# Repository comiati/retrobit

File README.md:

# RetroBit Game Console

This is a mix of retro game console with new technologies.

## Hardware

This is ARM9 processor running at 454Mhz with enough power to run linux and still in handsolder friendly TQFP package, which allow hobby DIY approach. RetroBit is even on 2 layer PCB and running at full speed.

######

- i.MX233 128-QFP Processor ARM926EJ-S runs up to 454MHz
- Memory 64MB DDR SDRAM (32Mx16)
- One USB host.
- Four input game pad controls.
- One degub UART.
- Composite video output.
- Stereo sound output.
- Micro SD Card.
- Power suply with power button and Led.
- Reset button.

## Software

ArchLinux package for the moment is with most advanced Kernel and enabled features so this is our choice for the moment to build examples.

This hardware is based on OLinuxXino of www.olimex.com
https://github.com/OLIMEX/OLINUXINO/tree/master/SOFTWARE/iMX233

For more informations send email to: fabianotraple@gmail.com

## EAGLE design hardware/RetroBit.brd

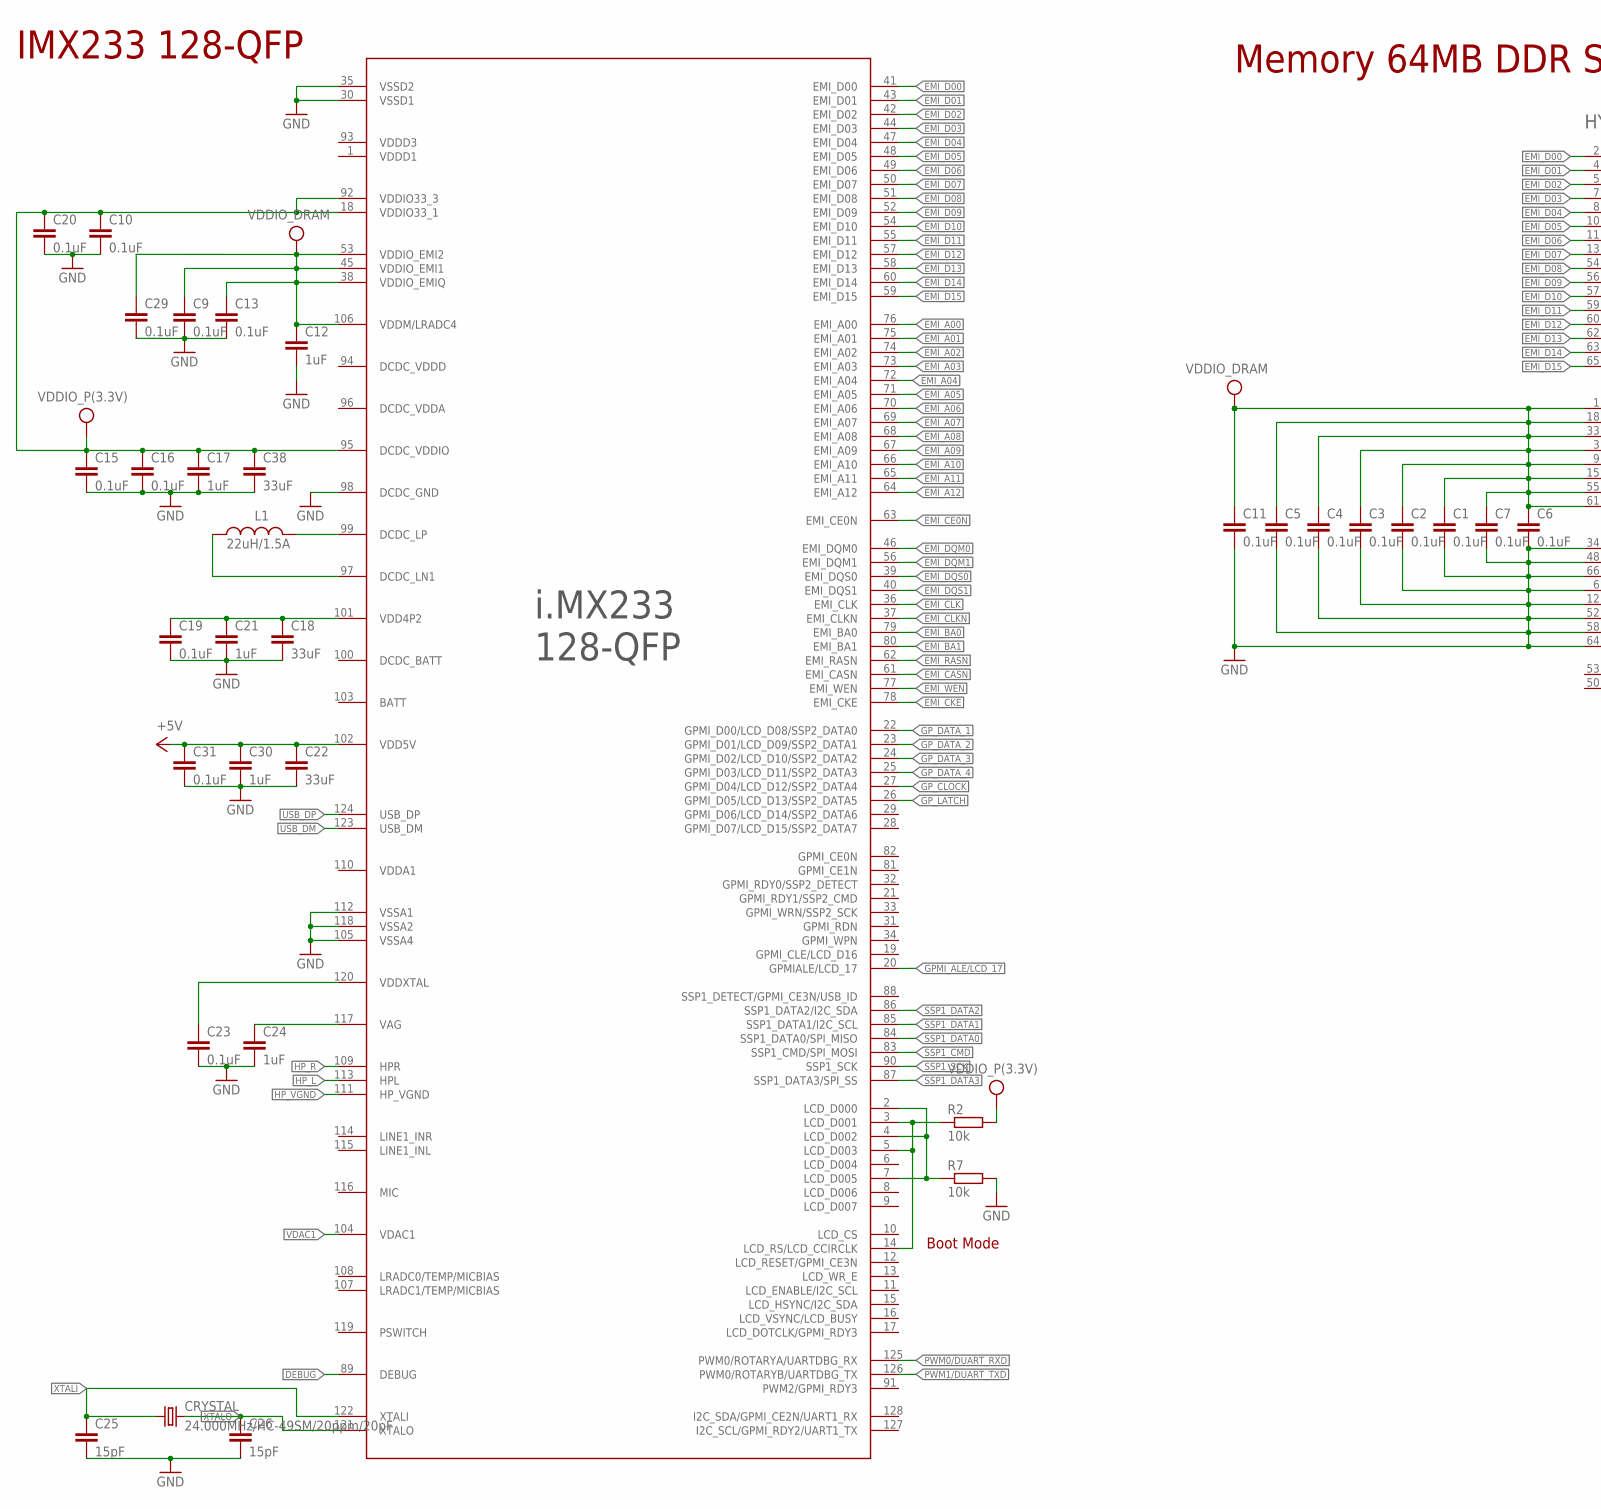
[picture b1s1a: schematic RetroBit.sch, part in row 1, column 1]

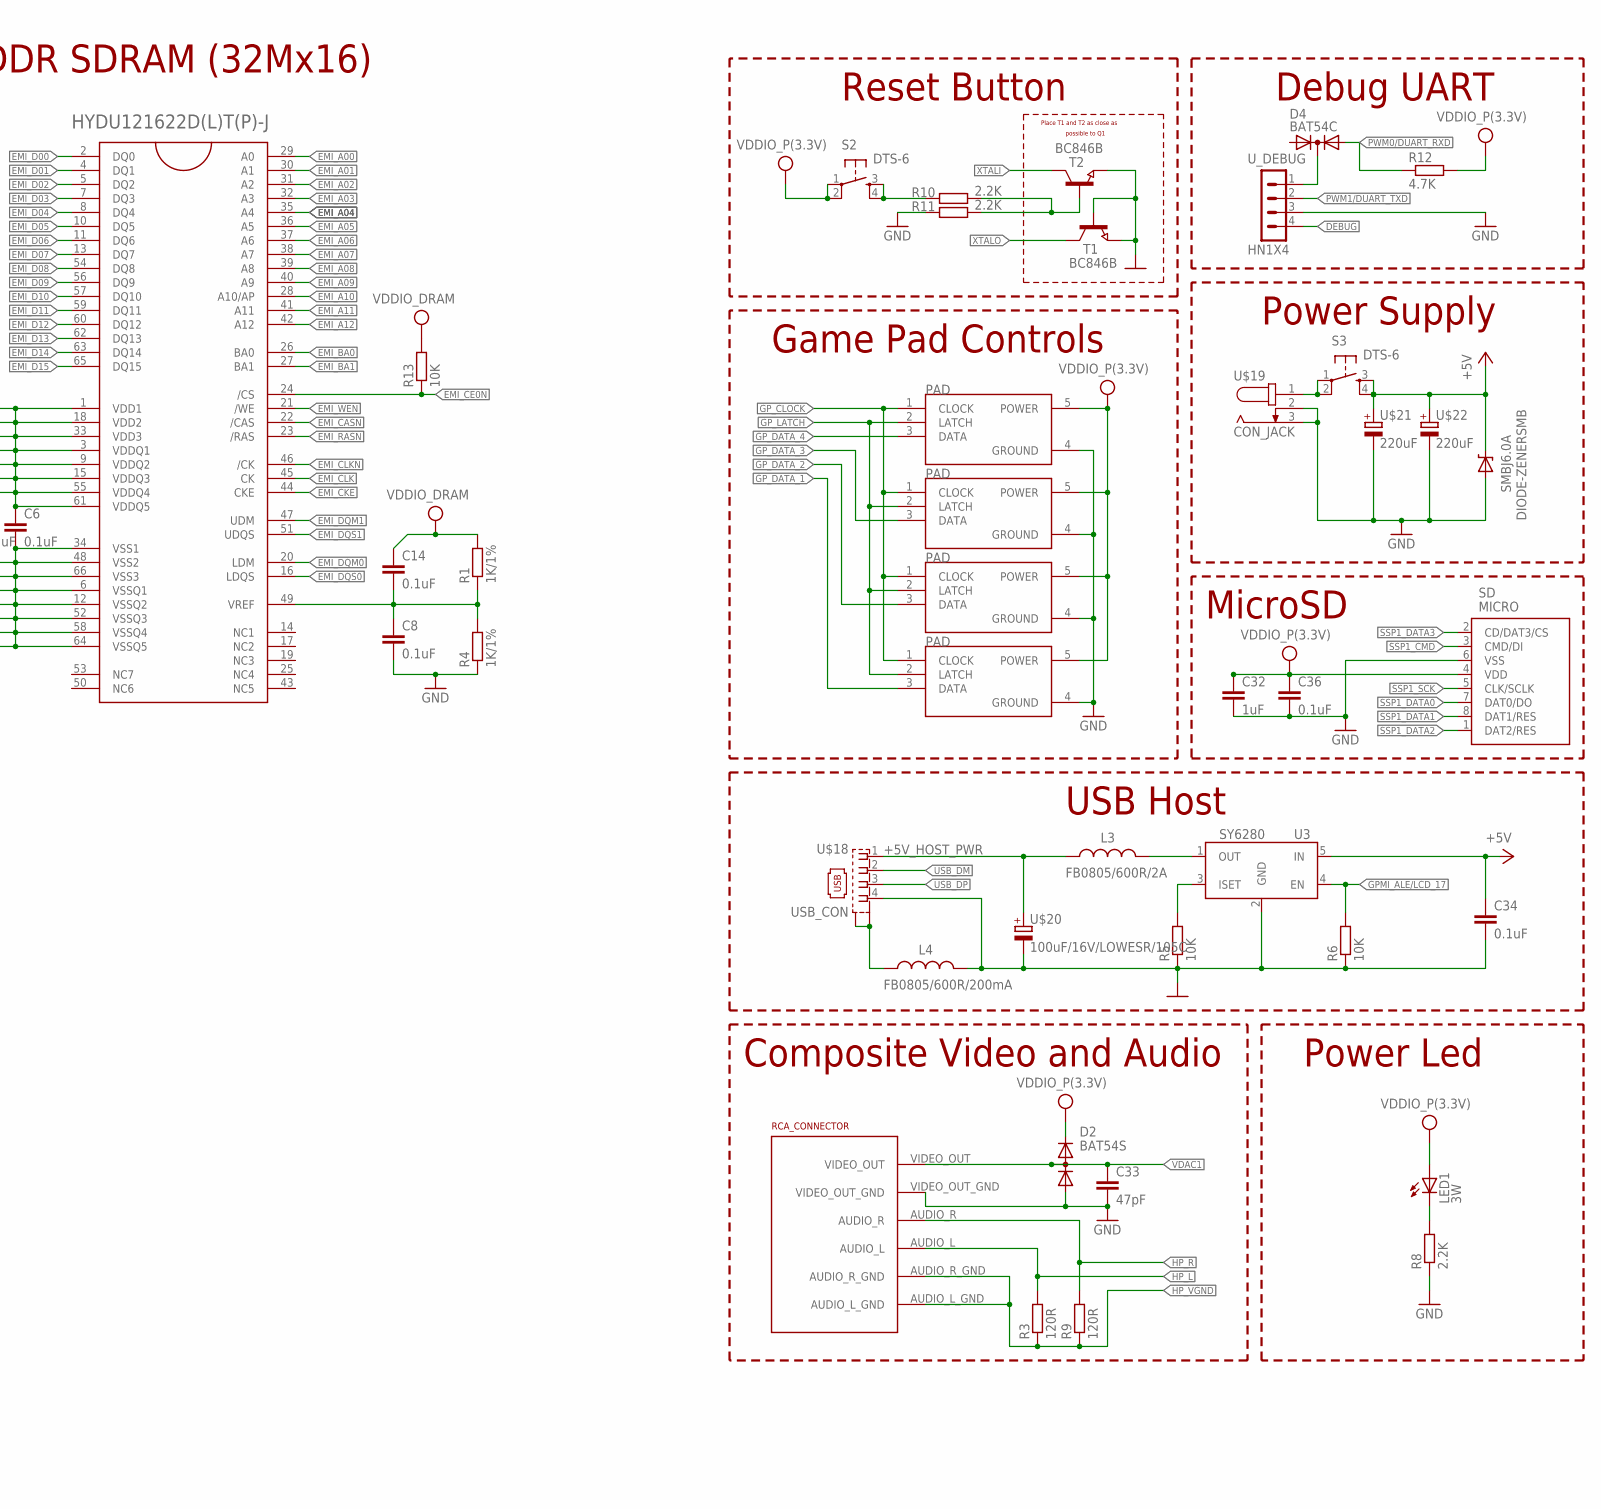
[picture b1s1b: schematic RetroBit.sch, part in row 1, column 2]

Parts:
C1, C2, C3, C4, C5, C6, C7, C8, C9, C10, C11, C13, C14, C15, C16, C19, C20, C23, C29, C31, C34, C36: 0.1uF; C0603K
C12, C17, C21, C24, C30, C32: 1uF; C0805K
C18, C22, C38: 33uF; C1210K
C25, C26: 15pF; C0603K
C33: 47pF; C0603K
CRYSTAL: 24.000MHz/HC-49SM/20ppm/20pF; HC49U-V
D2: BAT54S; SOT23C(BAT54S)
D4: BAT54C; SOT23C
IC1: MCIMX233CAG4C
L1: 22uH/1.5A; CR75
L3: FB0805/600R/2A; 0805
L4: FB0805/600R/200mA; 0805
LED1: 3W; LED3MM
R1, R4: 1K/1%; R0603
R2, R7: 10k; R0603
R3, R9: 120R; R0805
R5, R6, R13: 10K; R0805
R8, R10, R11: 2.2K; R0805
R12: 4.7K; R0805
RCA_CONNECTOR: RCA_CONNECTOR
S2, S3: DTS-6
SD: MICRO; TFR-MEM-CON
SMBJ6.0A: DIODE-ZENERSMB; SMB-DIODE
T1, T2: BC846B; SOT23
U3: SY6280; SOT23-5
U$1: HY5DU121622D; HYDU121622D(L)T(P)-J
U$3, U$8, U$9, U$14: GAME_PAD
U$18: USB_CON
U$19: CON_JACK
U$20: 100uF/16V/LOWESR/105C; CPOL-EVE-2.5,6-3
U$21, U$22: 220uF; CPOL-EVE-2.5,6-3
U_DEBUG: HN1X4

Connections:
+5V: C22.1, C30.1, C31.1, C34.1, IC1.102 (VDD5V), S3.3, S3.4, SMBJ6.0A.C, U3.5 (IN), U$21.+, U$22.+
+5V_HOST_PWR: L3.1, U$18.1, U$20.+
DEBUG: IC1.89 (DEBUG), U_DEBUG.4
EMI_A00: IC1.76 (EMI_A00), U$1.29 (A0)
EMI_A01: IC1.75 (EMI_A01), U$1.30 (A1)
EMI_A02: IC1.74 (EMI_A02), U$1.31 (A2)
EMI_A03: IC1.73 (EMI_A03), U$1.32 (A3)
EMI_A04: IC1.72 (EMI_A04), U$1.35 (A4)
EMI_A05: IC1.71 (EMI_A05), U$1.36 (A5)
EMI_A06: IC1.70 (EMI_A06), U$1.37 (A6)
EMI_A07: IC1.69 (EMI_A07), U$1.38 (A7)
EMI_A08: IC1.68 (EMI_A08), U$1.39 (A8)
EMI_A09: IC1.67 (EMI_A09), U$1.40 (A9)
EMI_A10: IC1.66 (EMI_A10), U$1.28 (A10/AP)
EMI_A11: IC1.65 (EMI_A11), U$1.41 (A11)
EMI_A12: IC1.64 (EMI_A12), U$1.42 (A12)
EMI_BA0: IC1.79 (EMI_BA0), U$1.26 (BA0)
EMI_BA1: IC1.80 (EMI_BA1), U$1.27 (BA1)
EMI_CASN: IC1.61 (EMI_CASN), U$1.22 (/CAS)
EMI_CE0N: IC1.63 (EMI_CE0N), R13.1, U$1.24 (/CS)
EMI_CKE: IC1.78 (EMI_CKE), U$1.44 (CKE)
EMI_CLK: IC1.36 (EMI_CLK), U$1.45 (CK)
EMI_CLKN: IC1.37 (EMI_CLKN), U$1.46 (/CK)
EMI_D00: IC1.41 (EMI_D00), U$1.2 (DQ0)
EMI_D01: IC1.43 (EMI_D01), U$1.4 (DQ1)
EMI_D02: IC1.42 (EMI_D02), U$1.5 (DQ2)
EMI_D03: IC1.44 (EMI_D03), U$1.7 (DQ3)
EMI_D04: IC1.47 (EMI_D04), U$1.8 (DQ4)
EMI_D05: IC1.48 (EMI_D05), U$1.10 (DQ5)
EMI_D06: IC1.49 (EMI_D06), U$1.11 (DQ6)
EMI_D07: IC1.50 (EMI_D07), U$1.13 (DQ7)
EMI_D08: IC1.51 (EMI_D08), U$1.54 (DQ8)
EMI_D09: IC1.52 (EMI_D09), U$1.56 (DQ9)
EMI_D10: IC1.54 (EMI_D10), U$1.57 (DQ10)
EMI_D11: IC1.55 (EMI_D11), U$1.59 (DQ11)
EMI_D12: IC1.57 (EMI_D12), U$1.60 (DQ12)
EMI_D13: IC1.58 (EMI_D13), U$1.62 (DQ13)
EMI_D14: IC1.60 (EMI_D14), U$1.63 (DQ14)
EMI_D15: IC1.59 (EMI_D15), U$1.65 (DQ15)
EMI_DQM0: IC1.46 (EMI_DQM0), U$1.20 (LDM)
EMI_DQM1: IC1.56 (EMI_DQM1), U$1.47 (UDM)
EMI_DQS0: IC1.39 (EMI_DQS0), U$1.16 (LDQS)
EMI_DQS1: IC1.40 (EMI_DQS1), U$1.51 (UDQS)
EMI_RASN: IC1.62 (EMI_RASN), U$1.23 (/RAS)
EMI_WEN: IC1.77 (EMI_WEN), U$1.21 (/WE)
GND: C1.2, C2.2, C3.2, C4.2, C5.2, C6.2, C7.2, C8.2, C9.2, C10.2, C11.2, C12.2, C13.2, C15.2, C16.2, C17.2, C18.2, C19.2, C20.2, C21.2, C22.2, C23.2, C24.2, C25.2, C26.2, C29.2, C30.2, C31.2, C32.2, C33.2, C34.2, C36.2, C38.2, D2.1 (A), IC1.30 (VSSD1), IC1.35 (VSSD2), IC1.98 (DCDC_GND), IC1.105 (VSSA4), IC1.112 (VSSA1), IC1.118 (VSSA2), L4.2, R4.1, R5.1, R6.1, R7.2, R8.1, R11.1, RCA_CONNECTOR.VIDEO_OUT_GND, SD.6 (VSS), SMBJ6.0A.A, T1.1 (B), T1.2 (E), T2.2 (E), U3.2 (GND), U$1.6 (VSSQ1), U$1.12 (VSSQ2), U$1.34 (VSS1), U$1.48 (VSS2), U$1.52 (VSSQ3), U$1.58 (VSSQ4), U$1.64 (VSSQ5), U$1.66 (VSS3), U$3.4 (GROUND), U$8.4 (GROUND), U$9.4 (GROUND), U$14.4 (GROUND), U$18.4, U$19.2, U$19.3 (1), U$20.-, U$21.-, U$22.-, U_DEBUG.3
GPMI_ALE/LCD_17: IC1.20 (GPMIALE/LCD_17), R6.2, U3.4 (EN)
GP_CLOCK: IC1.27 (GPMI_D04/LCD_D12/SSP2_DATA4), U$3.1 (CLOCK), U$8.1 (CLOCK), U$9.1 (CLOCK), U$14.1 (CLOCK)
GP_DATA_1: IC1.22 (GPMI_D00/LCD_D08/SSP2_DATA0), U$14.3 (DATA)
GP_DATA_2: IC1.23 (GPMI_D01/LCD_D09/SSP2_DATA1), U$9.3 (DATA)
GP_DATA_3: IC1.24 (GPMI_D02/LCD_D10/SSP2_DATA2), U$8.3 (DATA)
GP_DATA_4: IC1.25 (GPMI_D03/LCD_D11/SSP2_DATA3), U$3.3 (DATA)
GP_LATCH: IC1.26 (GPMI_D05/LCD_D13/SSP2_DATA5), U$3.2 (LATCH), U$8.2 (LATCH), U$9.2 (LATCH), U$14.2 (LATCH)
HP_L: IC1.113 (HPL), R3.2, RCA_CONNECTOR.AUDIO_L
HP_R: IC1.109 (HPR), R9.2, RCA_CONNECTOR.AUDIO_R
HP_VGND: IC1.111 (HP_VGND), R3.1, R9.1, RCA_CONNECTOR.AUDIO_L_GND, RCA_CONNECTOR.AUDIO_R_GND
unnamed: D4.3 (K), U_DEBUG.1
unnamed: C8.1, C14.2, R1.1, R4.2, U$1.49 (VREF)
unnamed: S3.1, S3.2, U$19.1 (3)
unnamed: C18.1, C19.1, C21.1, IC1.101 (VDD4P2)
unnamed: IC1.99 (DCDC_LP), L1.P$2 (2)
unnamed: IC1.3 (LCD_D001), IC1.5 (LCD_D003), IC1.14 (LCD_RS/LCD_CCIRCLK), R2.1
unnamed: IC1.97 (DCDC_LN1), L1.P$1 (1)
unnamed: R5.2, U3.3 (ISET)
unnamed: C23.1, IC1.120 (VDDXTAL)
unnamed: L3.2, U3.1 (OUT)
unnamed: L4.1, U$18.M1 (S1), U$18.M2 (S2)
unnamed: C24.1, IC1.117 (VAG)
unnamed: IC1.2 (LCD_D000), IC1.4 (LCD_D002), IC1.7 (LCD_D005), R7.1
unnamed: LED1.K (C), R8.2
unnamed: R10.1, S2.3, S2.4
unnamed: R10.2, R11.2, T2.1 (B)
PWM0/DUART_RXD: D4.2 (A2), IC1.125 (PWM0/ROTARYA/UARTDBG_RX), R12.1
PWM1/DUART_TXD: IC1.126 (PWM0/ROTARYB/UARTDBG_TX), U_DEBUG.2
SSP1_CMD: IC1.83 (SSP1_CMD/SPI_MOSI), SD.3 (CMD/DI)
SSP1_DATA0: IC1.84 (SSP1_DATA0/SPI_MISO), SD.7 (DAT0/DO)
SSP1_DATA1: IC1.85 (SSP1_DATA1/I2C_SCL), SD.8 (DAT1/RES)
SSP1_DATA2: IC1.86 (SSP1_DATA2/I2C_SDA), SD.1 (DAT2/RES)
SSP1_DATA3: IC1.87 (SSP1_DATA3/SPI_SS), SD.2 (CD/DAT3/CS)
SSP1_SCK: IC1.90 (SSP1_SCK), SD.5 (CLK/SCLK)
USB_DM: IC1.123 (USB_DM), U$18.2
USB_DP: IC1.124 (USB_DP), U$18.3
VDAC1: C33.1, D2.3 (AK), IC1.104 (VDAC1), RCA_CONNECTOR.VIDEO_OUT
VDDIO_DRAM: C1.1, C2.1, C3.1, C4.1, C5.1, C6.1, C7.1, C9.1, C11.1, C12.1, C13.1, C14.1, C29.1, IC1.38 (VDDIO_EMIQ), IC1.45 (VDDIO_EMI1), IC1.53 (VDDIO_EMI2), IC1.106 (VDDM/LRADC4), R1.2, R13.2, U$1.1 (VDD1), U$1.3 (VDDQ1), U$1.9 (VDDQ2), U$1.15 (VDDQ3), U$1.18 (VDD2), U$1.33 (VDD3), U$1.55 (VDDQ4), U$1.61 (VDDQ5)
VDDIO_P(3.3V): C10.1, C15.1, C16.1, C17.1, C20.1, C32.1, C36.1, C38.1, D2.2 (K), IC1.18 (VDDIO33_1), IC1.92 (VDDIO33_3), IC1.95 (DCDC_VDDIO), LED1.A, R2.2, R12.2, S2.1, S2.2, SD.4 (VDD), U$3.5 (POWER), U$8.5 (POWER), U$9.5 (POWER), U$14.5 (POWER)
XTALI: C25.1, CRYSTAL.1, IC1.122 (XTALI), T2.3 (C)
XTALO: C26.1, CRYSTAL.2, IC1.121 (XTALO), T1.3 (C)

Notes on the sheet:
MicroSD
Place T1 and T2 as close as
possible to Q1
Reset Button
Boot Mode
Game Pad Controls
Memory 64MB DDR SDRAM (32Mx16)
Power Supply
USB Host
Composite Video and Audio
Power Led
Debug UART
IMX233 128-QFP

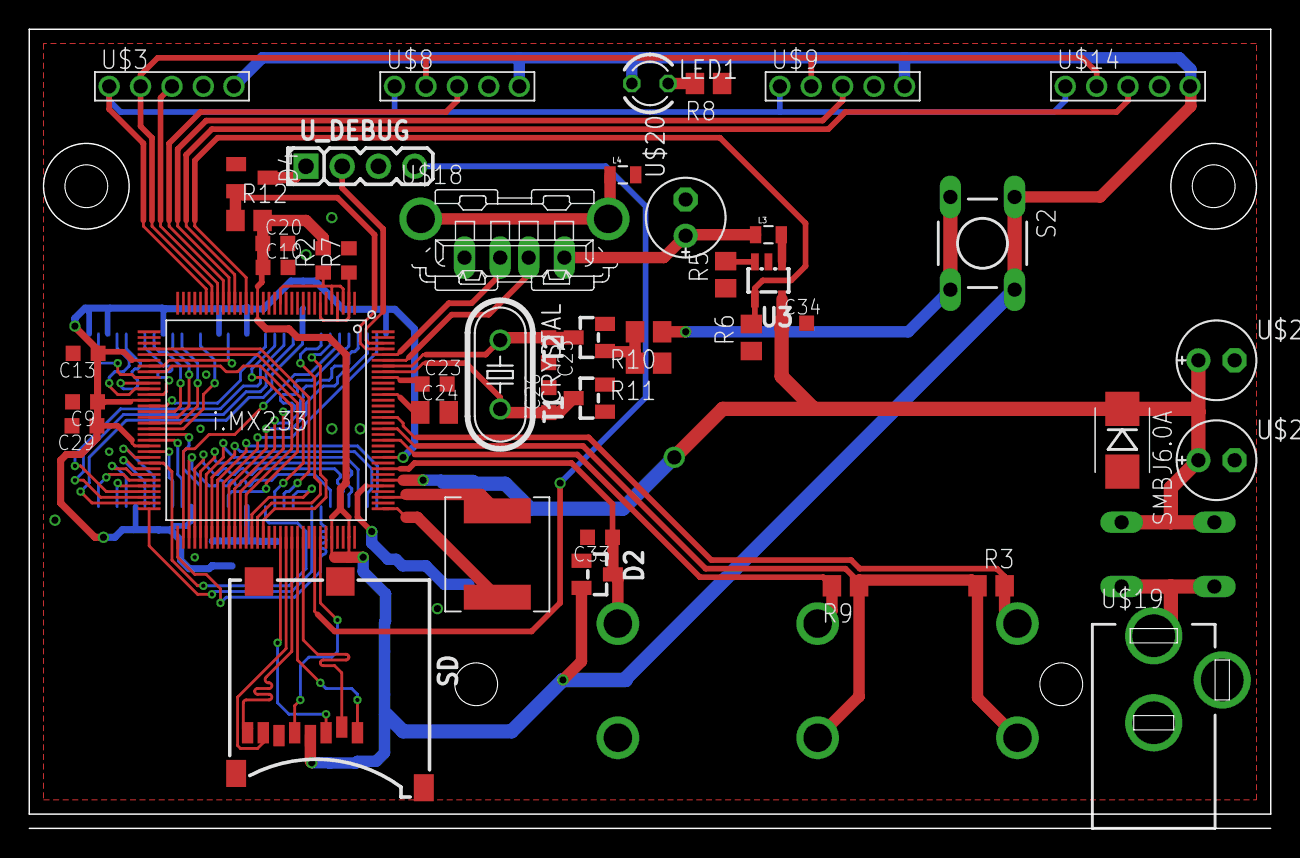
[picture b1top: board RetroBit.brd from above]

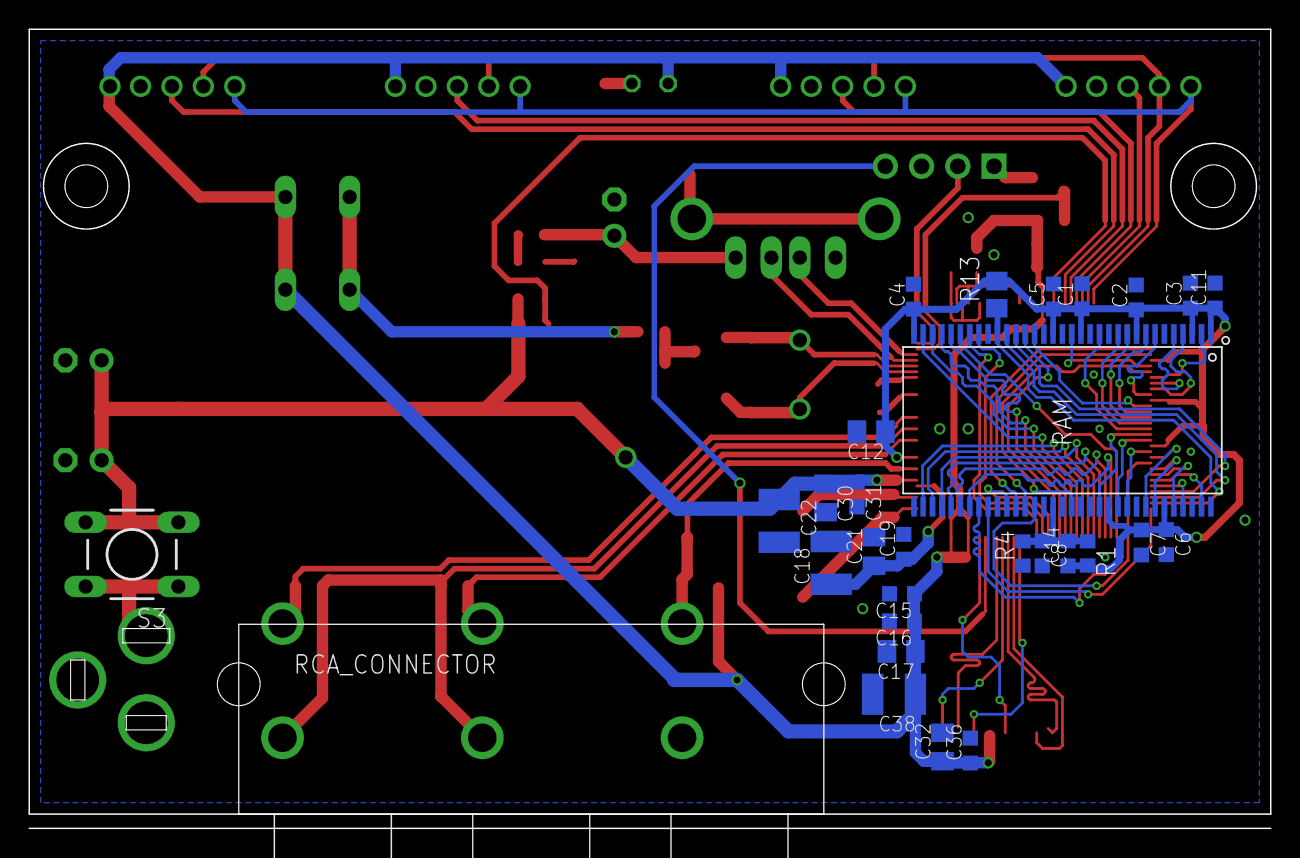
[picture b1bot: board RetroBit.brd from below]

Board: 2 copper layers, 87.0 x 56.0 mm, 74 parts (29 on the bottom side), 87 nets.

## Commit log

2016-09-09 First commit!
2016-09-09 Add new image to readme.

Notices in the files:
parts and their libraries:
SparkFun-DiscreteSemi: Licensing: CC v3.0 Share-Alike You are welcome to use this library for commercial purposes.
